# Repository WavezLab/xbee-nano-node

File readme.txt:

Eagle PCB files for Xbee-Nano Node.
Imported from BitBucket Repository.
Simple and Small Wireless Node using Arduino Nano and Xbee RF module on a single Board.

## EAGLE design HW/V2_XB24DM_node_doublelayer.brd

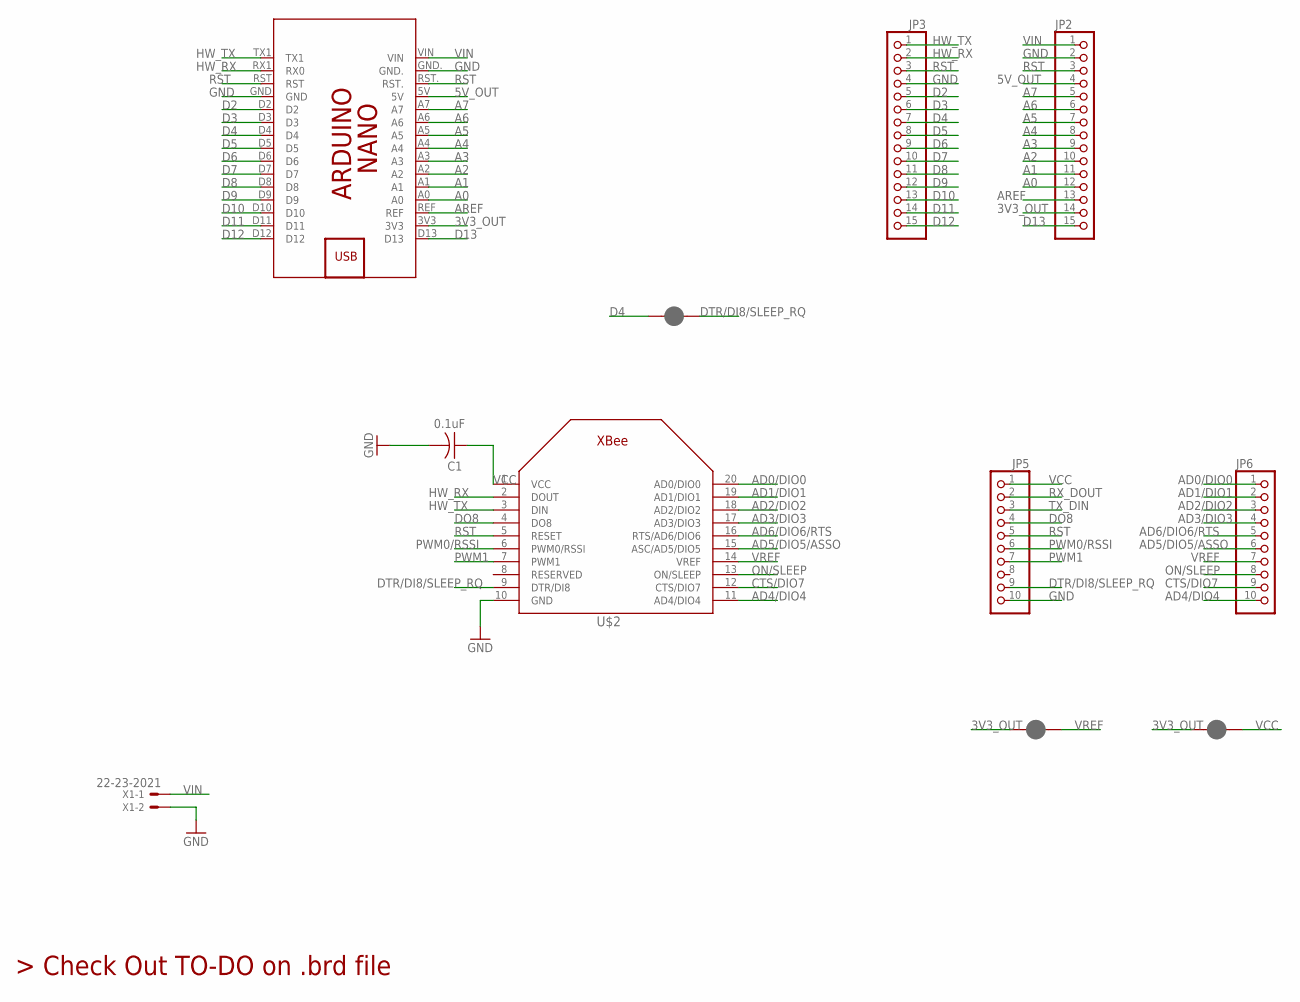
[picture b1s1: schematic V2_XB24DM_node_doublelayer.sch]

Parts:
C1: 0.1uF; C1206
JP1, JP4, JP7: JUMPER-PAD-2-NC_BY_PASTEFULL-BOX-SILK; PAD-JUMPER-2-NC_BY_PASTE_YES_SILK_FULL_BOX
JP2, JP3: PINHD-1X15; 1X15
JP5, JP6: PINHD-1X10; 1X10
PCB1: ARDUINO_NANO
U$2: XBEE
X1: 22-23-2021

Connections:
3V3_OUT: JP1.1, JP2.14, JP7.1, PCB1.3V3
5V_OUT: JP2.4, PCB1.5V
A0: JP2.12, PCB1.A0
A1: JP2.11, PCB1.A1
A2: JP2.10, PCB1.A2
A3: JP2.9, PCB1.A3
A4: JP2.8, PCB1.A4
A5: JP2.7, PCB1.A5
A6: JP2.6, PCB1.A6
A7: JP2.5, PCB1.A7
AD0/DIO0: JP6.1, U$2.20 (AD0/DIO0)
AD1/DIO1: JP6.2, U$2.19 (AD1/DIO1)
AD2/DIO2: JP6.3, U$2.18 (AD2/DIO2)
AD3/DIO3: JP6.4, U$2.17 (AD3/DIO3)
AD4/DIO4: JP6.10, U$2.11 (AD4/DIO4)
AD5/DIO5/ASSO: JP6.6, U$2.15 (ASC/AD5/DIO5)
AD6/DIO6/RTS: JP6.5, U$2.16 (RTS/AD6/DIO6)
AREF: JP2.13, PCB1.REF
CTS/DIO7: JP6.9, U$2.12 (CTS/DIO7)
D2: JP3.5, PCB1.D2
D3: JP3.6, PCB1.D3
D4: JP3.7, JP4.1, PCB1.D4
D5: JP3.8, PCB1.D5
D6: JP3.9, PCB1.D6
D7: JP3.10, PCB1.D7
D8: JP3.11, PCB1.D8
D9: JP3.12, PCB1.D9
D10: JP3.13, PCB1.D10
D11: JP3.14, PCB1.D11
D12: JP3.15, PCB1.D12
D13: JP2.15, PCB1.D13
DO8: JP5.4, U$2.4 (DO8)
DTR/DI8/SLEEP_RQ: JP4.2, JP5.9, U$2.9 (DTR/DI8)
GND: C1.2, JP2.2, JP3.4, JP5.10, PCB1.GND, PCB1.GND., U$2.10 (GND), X1.2
HW_RX: JP3.2, PCB1.RX1 (RX0), U$2.2 (DOUT)
HW_TX: JP3.1, PCB1.TX1, U$2.3 (DIN)
ON/SLEEP: JP6.8, U$2.13 (ON/SLEEP)
PWM0/RSSI: JP5.6, U$2.6 (PWM0/RSSI)
PWM1: JP5.7, U$2.7 (PWM1)
RST: JP2.3, JP3.3, JP5.5, PCB1.RST, PCB1.RST., U$2.5 (RESET)
RX_DOUT: JP5.2
TX_DIN: JP5.3
VCC: C1.1, JP1.2, JP5.1, U$2.1 (VCC)
VIN: JP2.1, PCB1.VIN, X1.1
VREF: JP6.7, JP7.2, U$2.14 (VREF)

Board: 2 copper layers, 11 parts (4 on the bottom side), 43 nets, no tracks yet.

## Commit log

2017-01-07 Hello first commit
2017-01-07 locations created online with Bitbucket
2017-01-07 making changes in a branch
2017-01-07 V2 added
2017-01-26 Updated with little description

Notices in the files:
parts and their libraries:
SparkFun-Passives: Licensing: Creative Commons ShareAlike 4.0 International - https://creativecommons.org/licenses/by-sa/4.0
